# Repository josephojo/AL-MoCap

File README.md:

# AL-MoCap
Unity-Based MoCap System implemented on Firebase and linked to a web-app. The web-app acts as a medium for issuing injury risk reports to an employer. Includes PCB designs for Hardware.

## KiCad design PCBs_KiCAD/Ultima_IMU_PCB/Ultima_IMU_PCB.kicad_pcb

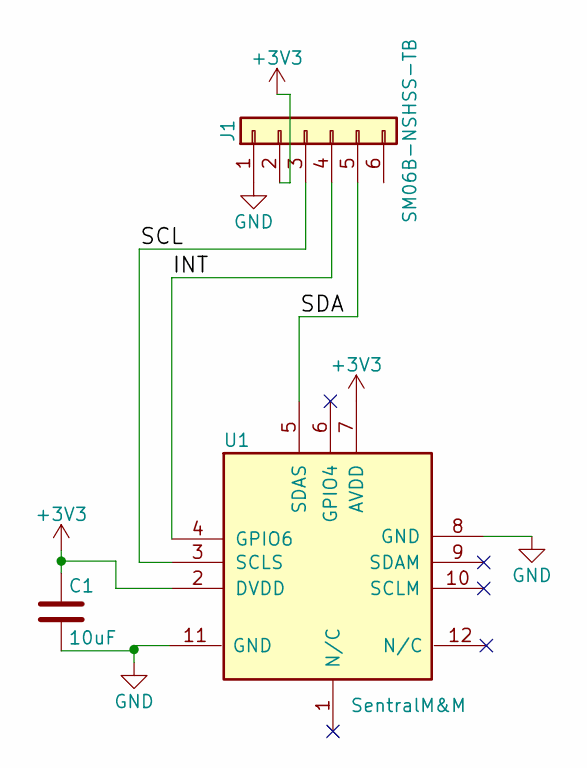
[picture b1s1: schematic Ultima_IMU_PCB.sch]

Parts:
C1: 10uF; C_Disc_D3.0mm_W2.0mm_P2.50mm
J1: SM06B-NSHSS-TB
U1: SentralM&M

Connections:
+3V3: C1.1, J1.2, U1.2 (DVDD), U1.7 (AVDD)
/INT: J1.4, U1.4 (GPIO6)
/SCL: J1.3, U1.3 (SCLS)
/SDA: J1.5, U1.5 (SDAS)
GND: C1.2, J1.1, U1.8 (GND), U1.11 (GND)

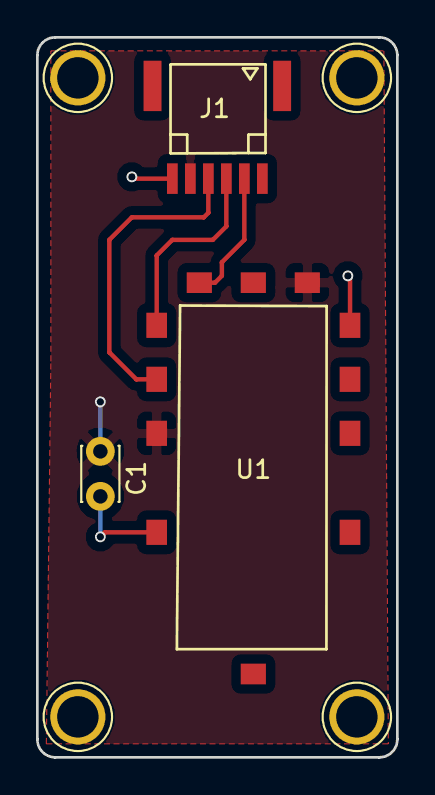
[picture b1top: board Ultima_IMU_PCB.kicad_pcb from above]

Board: 2 copper layers, 20.0 x 40.0 mm, 3 parts (0 on the bottom side), 5 nets.

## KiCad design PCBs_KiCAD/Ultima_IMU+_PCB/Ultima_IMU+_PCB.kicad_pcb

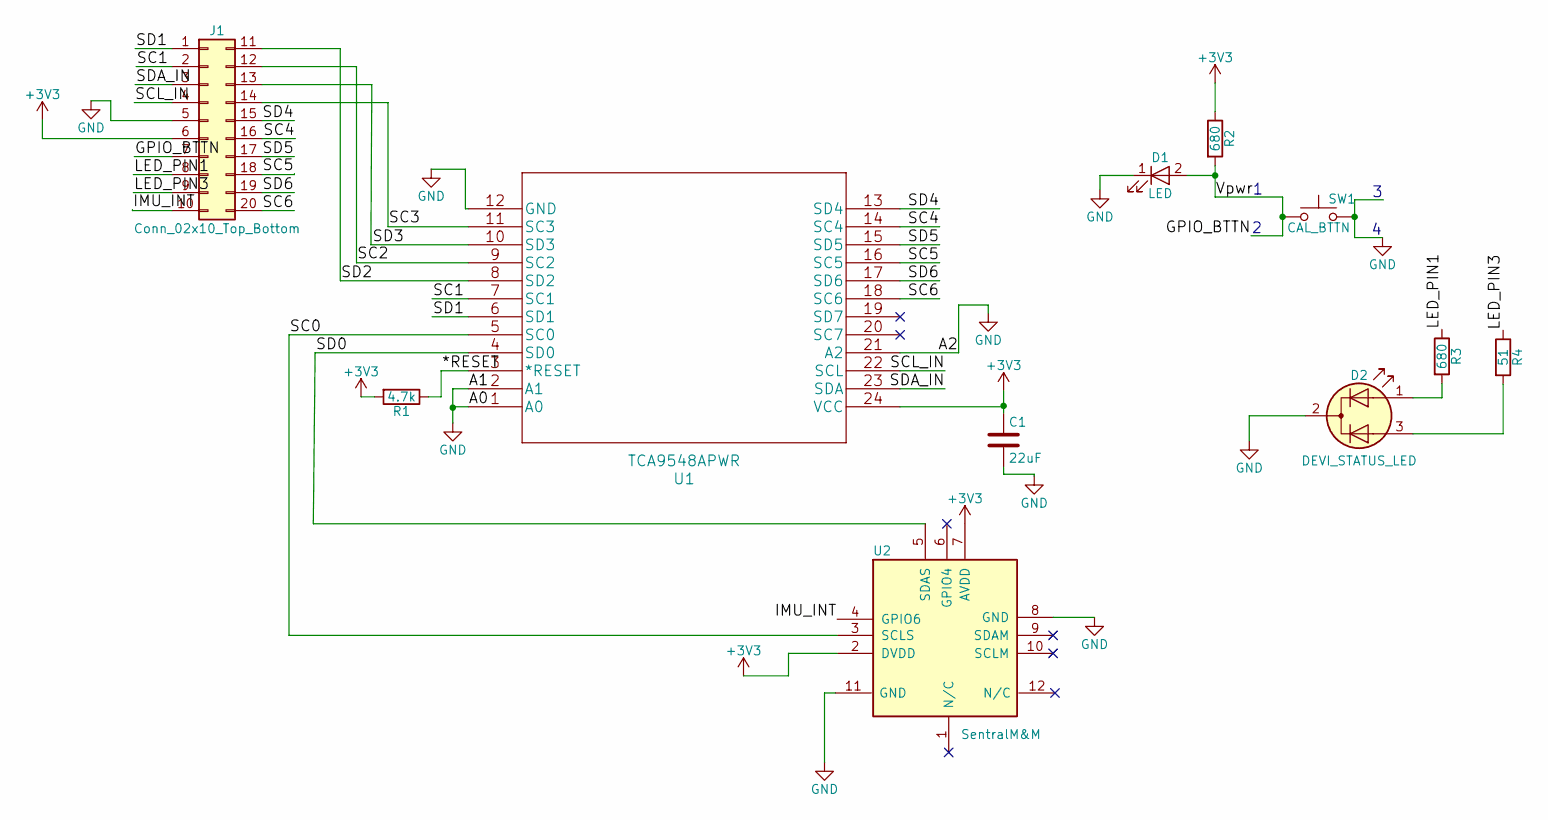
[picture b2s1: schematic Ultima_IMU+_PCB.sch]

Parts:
C1: 22uF; C_Disc_D3.0mm_W2.0mm_P2.50mm
D1: LED; LED_D3.0mm
D2: DEVI_STATUS_LED; LED_D3.0mm-3
J1: Conn_02x10_Top_Bottom; SM20B-ZPDSS-TF
R1: 4.7k; R_Axial_DIN0204_L3.6mm_D1.6mm_P2.54mm_Vertical
R2, R3: 680; R_Axial_DIN0204_L3.6mm_D1.6mm_P2.54mm_Vertical
R4: 51; R_Axial_DIN0204_L3.6mm_D1.6mm_P2.54mm_Vertical
SW1: CAL_BTTN; SW_PUSH_6mm_h13mm
U1: TCA9548APWR
U2: SentralM&M

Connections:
+3V3: C1.1, J1.6, R1.2, R2.1, U1.24 (VCC), U2.2 (DVDD), U2.7 (AVDD)
/*RESET: R1.1, U1.3 (*RESET)
/GPIO_BTTN: D1.2 (A), J1.7, R2.2, SW1.1
/IMU_INT: J1.10, U2.4 (GPIO6)
/LED_PIN1: J1.8, R3.1
/LED_PIN3: J1.9, R4.1
/SC0: U1.5 (SC0), U2.3 (SCLS)
/SC1: J1.2, U1.7 (SC1)
/SC2: J1.12, U1.9 (SC2)
/SC3: J1.14, U1.11 (SC3)
/SC4: J1.16, U1.14 (SC4)
/SC5: J1.18, U1.16 (SC5)
/SC6: J1.20, U1.18 (SC6)
/SCL_IN: J1.4, U1.22 (SCL)
/SD0: U1.4 (SD0), U2.5 (SDAS)
/SD1: J1.1, U1.6 (SD1)
/SD2: J1.11, U1.8 (SD2)
/SD3: J1.13, U1.10 (SD3)
/SD4: J1.15, U1.13 (SD4)
/SD5: J1.17, U1.15 (SD5)
/SD6: J1.19, U1.17 (SD6)
/SDA_IN: J1.3, U1.23 (SDA)
GND: C1.2, D1.1 (K), D2.2 (K), J1.5, SW1.2, U1.1 (A0), U1.2 (A1), U1.12 (GND), U1.21 (A2), U2.8 (GND), U2.11 (GND)
unnamed: D2.1 (A1), R3.2
unnamed: D2.3 (A2), R4.2

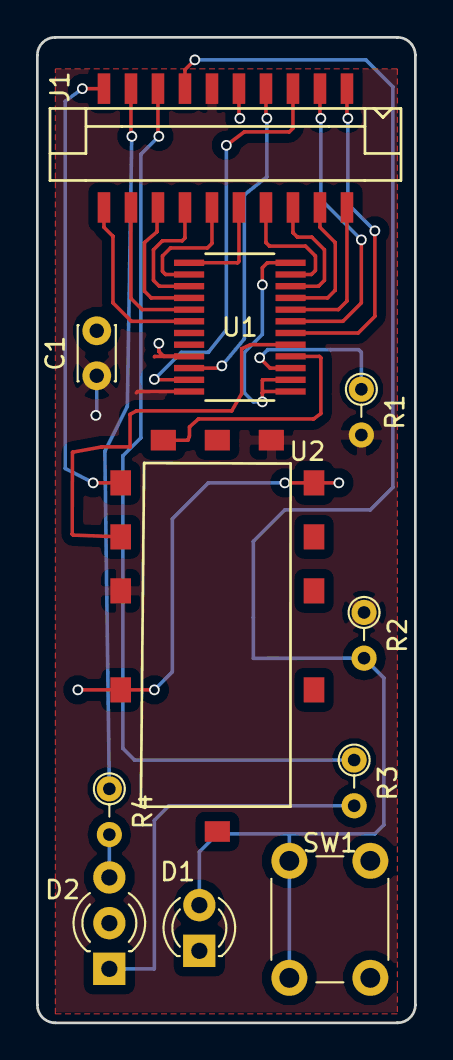
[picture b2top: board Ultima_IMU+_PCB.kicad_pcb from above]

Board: 2 copper layers, 21.0 x 54.8 mm, 11 parts (0 on the bottom side), 25 nets.

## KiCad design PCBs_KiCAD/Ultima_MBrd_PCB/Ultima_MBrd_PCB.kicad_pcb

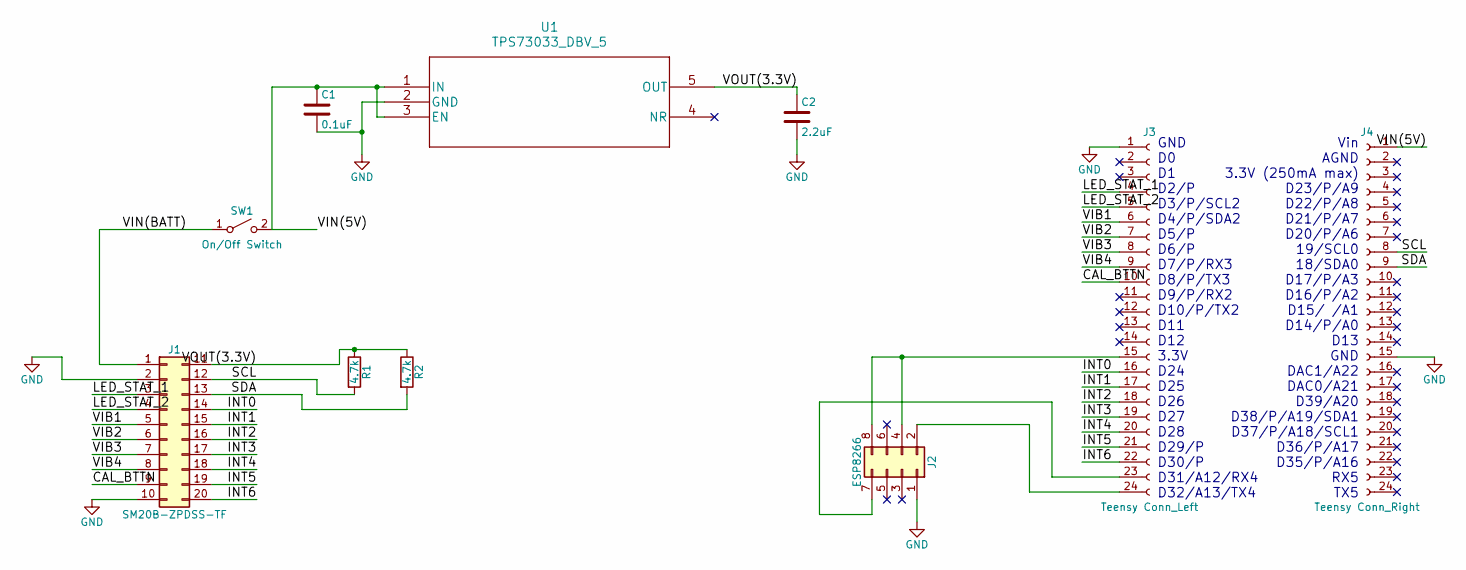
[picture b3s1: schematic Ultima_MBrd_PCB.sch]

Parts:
C1: 0.1uF; C_Disc_D3.0mm_W2.0mm_P2.50mm
C2: 2.2uF; C_Disc_D3.0mm_W2.0mm_P2.50mm
J1: SM20B-ZPDSS-TF
J2: ESP8266; Pin_Header_Straight_2x04_Pitch2.54mm
J3: Teensy Conn_Left; Pin_Header_Straight_1x24_Pitch2.54mm
J4: Teensy Conn_Right; Pin_Header_Straight_1x24_Pitch2.54mm
R1, R2: 4.7k; R_Axial_DIN0204_L3.6mm_D1.6mm_P2.54mm_Vertical
SW1: On/Off Switch; Pin_Header_Straight_1x02_Pitch2.54mm
U1: TPS73033_DBV_5; TPS73033DBVR

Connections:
/CAL_BTTN: J1.9, J3.10
/INT0: J1.14, J3.16
/INT1: J1.15, J3.17
/INT2: J1.16, J3.18
/INT3: J1.17, J3.19
/INT4: J1.18, J3.20
/INT5: J1.19, J3.21
/INT6: J1.20, J3.22
/LED_STAT_1: J1.3, J3.4
/LED_STAT_2: J1.4, J3.5
/SCL: J1.12, J4.8, R1.2
/SDA: J1.13, J4.9, R2.2
/VIB1: J1.5, J3.6
/VIB2: J1.6, J3.7
/VIB3: J1.7, J3.8
/VIB4: J1.8, J3.9
/VIN(5V): C1.1, J4.1, SW1.2 (B), U1.1 (IN), U1.3 (EN)
/VIN(BATT): J1.1, SW1.1 (A)
/VOUT(3.3V): C2.1, J1.11, R1.1, R2.1, U1.5 (OUT)
GND: C1.2, C2.2, J1.2, J1.10, J2.1, J3.1, J4.15, U1.2 (GND)
unnamed: J2.2, J3.24
unnamed: J2.4, J2.8, J3.15
unnamed: J2.7, J3.23

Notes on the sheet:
Vin AGND 3.3V (250mA max) D23/P/A9 D22/P/A8 D21/P/A7 D20/P/A6 19/SCL0 18/SDA0 D17/P/A3 D16/P/A2 D15/ /A1 D14/P/A0 D13 GND DAC1/A22 DAC0/A21 D39/A20 D38/P/A19/SDA1 D37/P/A18/SCL1 D36/P/A17 D35/P/A16 RX5 TX5
GND D0 D1 D2/P D3/P/SCL2 D4/P/SDA2 D5/P D6/P D7/P/RX3 D8/P/TX3 D9/P/RX2 D10/P/TX2 D11 D12 3.3V D24 D25 D26 D27 D28 D29/P D30/P D31/A12/RX4 D32/A13/TX4

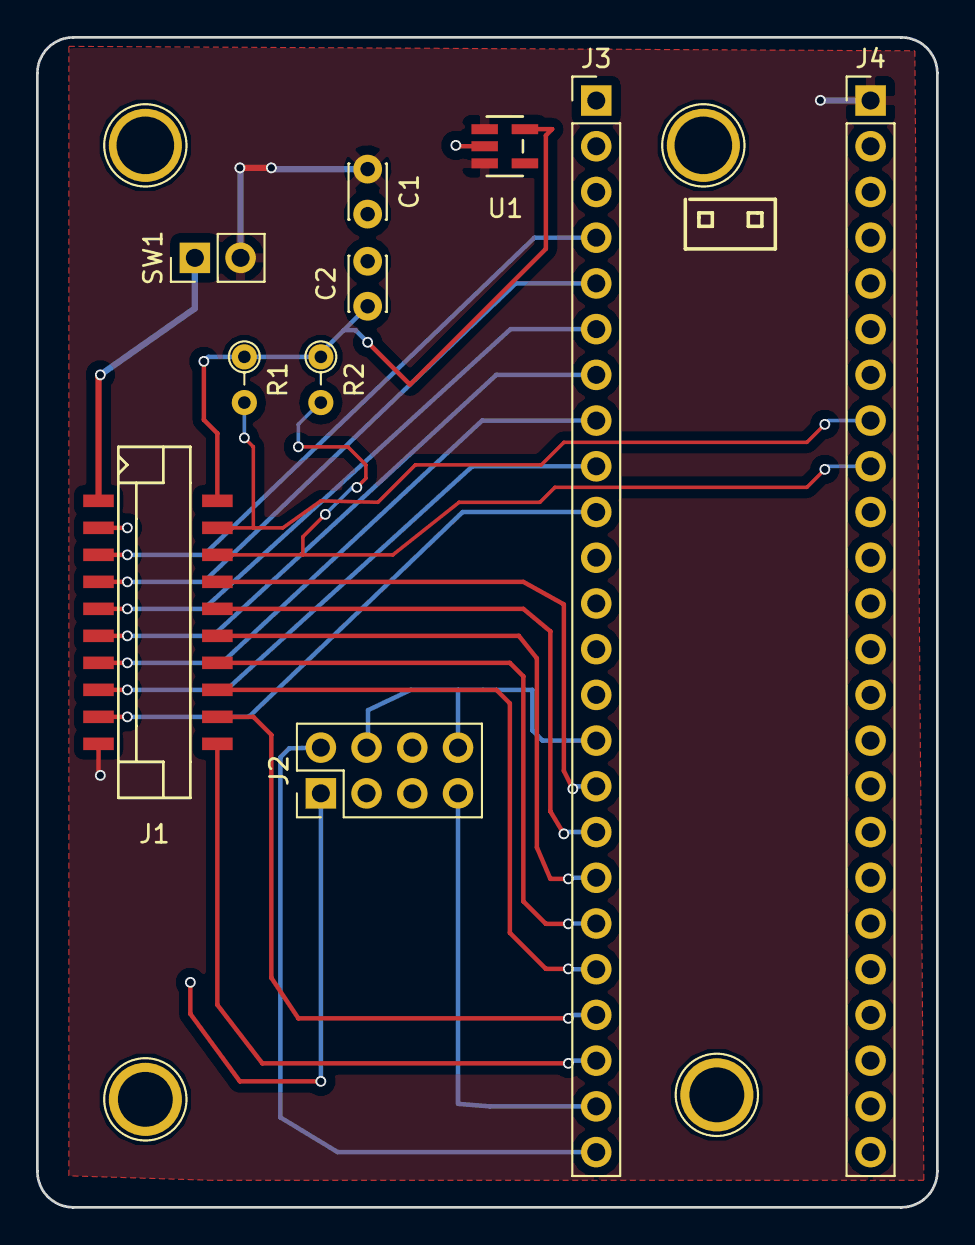
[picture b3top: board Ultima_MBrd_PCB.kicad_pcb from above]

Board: 2 copper layers, 50.0 x 65.0 mm, 10 parts (0 on the bottom side), 23 nets.

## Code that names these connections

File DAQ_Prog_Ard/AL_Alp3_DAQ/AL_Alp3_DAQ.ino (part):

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// ########### Pin Definitions ############
#define BLUE_LED 2 // LED Indicator pin
#define RED_LED 3 // LED Indicator pin
#define VIB1_PIN 4
#define VIB2_PIN 5
#define VIB3_PIN 6
#define VIB4_PIN 7
#define BUTTON_INT 8
#define SENTRAL0_INT 23
#define SENTRAL1_INT 25
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
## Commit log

2018-03-09 Added Folders anf Files
    Added PCB, Ard, Unity and Blender Folders
2018-03-12 First real rev of the DAQ prog
2018-03-21 Implemented Backend Algorithms for one emplyee (user) excluding
2018-03-21 Fixed bug with algorithms
    Bugs include:
    - Retrieving an old data capture on startup
    - sending out occurences on wrong intervlas
2018-03-23 Updated Database location for Occurences
2018-03-23 Merged TestDaq to branch
2018-03-23 Configured for single sensor data capture
2018-03-25 Added some finishing touches to be merged with master
2018-03-25 changed wording
2018-03-25 finishing touches
2018-03-26 not much
2018-03-26 added movierecorder object to use for recording gifs
2018-03-27 Added a routine to send some sensor data from "RunAlgorithms". Also, removed the UTJ example.
2018-03-28 testing retrieval functionality
2018-03-28 uncommented the data
2018-03-28 random stuff
2018-03-28 added nodeMCU.ino for wifi comm to firebase
2018-03-28 Added Firebase and ESP Libraries
2018-03-28 Json Files for Arduino
2018-03-28 removed ESP8266 device folder
2018-03-29 Made changes to data transmission format from the DAQ, and implemented data de-formatting and transmission to firebase
2018-03-29 Used thread to upload data instead of task
2018-03-29 Updated GIT
2018-03-30 Experimenting
2018-03-30 First attempt at trying to improve occurence updates
2018-03-30 Second attempt at trying to implement the occurence update functions
2018-03-30 Added Serial4 for data transmission instead of serial
2018-04-01 Cleaned up a bit of RunAlgo, and got the datetime retrieval on NodeMCU to work
2018-04-01 NodeMCU code works
2018-04-02 Debugging Attempt 1
2018-04-03 Trying to fix problem with sending data. Only sends 2 or 4 at a time and data is missing qw ofr them. the val is 0;
2018-04-03 Moved the buffer initialization line for the jsonBuffer (sensorBuff) near it's implementation.
    - Buffer was running out of room that's why it'd stop sending out data.
2018-04-03 idk, stuff?
2018-04-05 Added delays to nodeMCU cuz the wifi/tcp/ip internal routines work then. Increased the processor speed of the NODEMCU and moved the code for sending data to within the condition that sees a newline
2018-04-05 Fixed calibration boucing issue (bttn), bumped up serial communication to 115200 for faster comm, increased the clockspeed of nodeMCU chip. Motion capture on this is the most "realtime" we've had.Tha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
2018-04-06 Added function that deletes data as they come in
2018-04-06 Added routine to notify the user when the wifi is out
2018-04-09 Aded blinking LED to NodeMCU, [ERM]changed shoulder limits to 0 from 500

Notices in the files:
parts and their libraries:
Copyright 2016 Accelerated Designs. All rights reserved.
